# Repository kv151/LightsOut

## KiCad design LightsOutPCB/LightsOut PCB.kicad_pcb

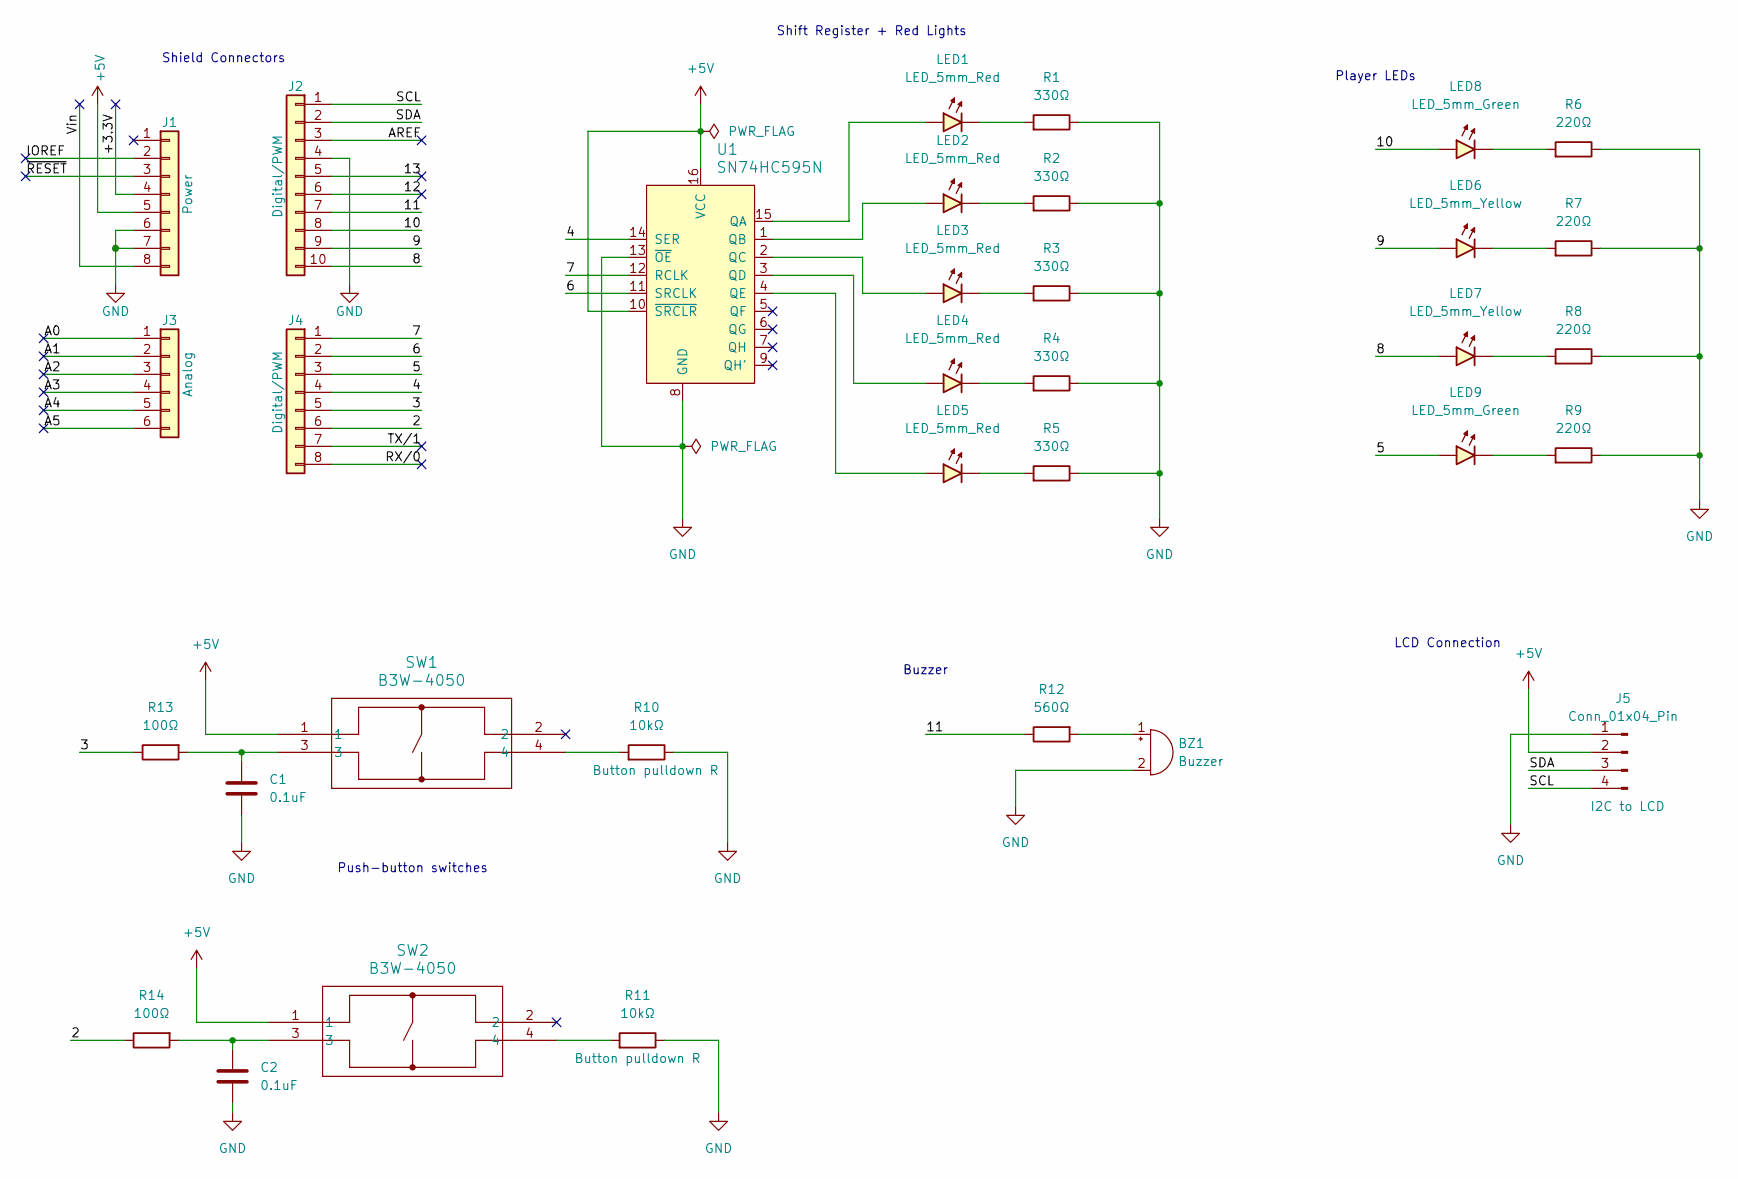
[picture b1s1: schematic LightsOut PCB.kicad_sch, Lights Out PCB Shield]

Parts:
BZ1: Buzzer; MagneticBuzzer_StarMicronics_TMB
C1, C2: 0.1uF; C_Radial_D5.0mm_H7.0mm_P2.00mm
J1: Power; PinSocket_1x08_P2.54mm_Vertical
J2: Digital/PWM; PinSocket_1x10_P2.54mm_Vertical
J3: Analog; PinSocket_1x06_P2.54mm_Vertical
J4: Digital/PWM; PinSocket_1x08_P2.54mm_Vertical
J5: Conn_01x04_Pin; PinSocket_1x04_P2.00mm_Vertical
LED1, LED2, LED3, LED4, LED5: LED_5mm_Red; LED_D5.0mm
LED6, LED7: LED_5mm_Yellow; LED_D5.0mm
LED8, LED9: LED_5mm_Green; LED_D5.0mm
R1, R2, R3, R4, R5: 330Ω; R_Axial_DIN0204_L3.6mm_D1.6mm_P7.62mm_Horizontal
R6, R7, R8, R9: 220Ω; R_Axial_DIN0204_L3.6mm_D1.6mm_P7.62mm_Horizontal
R10, R11: 10kΩ; R_Axial_DIN0204_L3.6mm_D1.6mm_P7.62mm_Horizontal
R12: 560Ω; R_Axial_DIN0204_L3.6mm_D1.6mm_P7.62mm_Horizontal
R13, R14: 100Ω; R_Axial_DIN0204_L3.6mm_D1.6mm_P7.62mm_Horizontal
SW1, SW2: B3W-4050; SW_B3W-4050_OMR
U1: SN74HC595N; DIP-16_W7.62mm; MPN SN74HC595N; Digi-Key_PN 296-1600-5-ND

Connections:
+5V: J1.5, J5.2, SW1.1, SW2.1, U1.10 (~SRCLR), U1.16 (VCC)
/2: J4.6, R14.2
/3: J4.5, R13.2
/4: J4.4, U1.14 (SER)
/5: J4.3, LED9.2 (A)
/6: J4.2, U1.11 (SRCLK)
/7: J4.1, U1.12 (RCLK)
/8: J2.10, LED7.2 (A)
/9: J2.9, LED6.2 (A)
/10: J2.8, LED8.2 (A)
/11: J2.7, R12.2
/12: J2.6
/13: J2.5
/+3.3V: J1.4
/A0: J3.1
/A1: J3.2
/A2: J3.3
/A3: J3.4
/A4: J3.5
/A5: J3.6
/AREF: J2.3
/IOREF: J1.2
/RX/0: J4.8
/SCL: J2.1, J5.4
/SDA: J2.2, J5.3
/TX/1: J4.7
/Vin: J1.8
/~RESET: J1.3
GND: BZ1.2 (-), C1.2, C2.2, J1.6, J1.7, J2.4, J5.1, R1.2, R2.2, R3.2, R4.2, R5.2, R6.2, R7.2, R8.2, R9.2, R10.2, R11.2, U1.8 (GND), U1.13 (~OE)
unnamed: BZ1.1 (+), R12.1
unnamed: C1.1, R13.1, SW1.3
unnamed: C2.1, R14.1, SW2.3
unnamed: LED1.2 (A), U1.15 (QA)
unnamed: LED1.1 (K), R1.1
unnamed: LED2.2 (A), U1.1 (QB)
unnamed: LED2.1 (K), R2.1
unnamed: LED3.2 (A), U1.2 (QC)
unnamed: LED3.1 (K), R3.1
unnamed: LED4.2 (A), U1.3 (QD)
unnamed: LED4.1 (K), R4.1
unnamed: LED5.2 (A), U1.4 (QE)
unnamed: LED5.1 (K), R5.1
unnamed: LED6.1 (K), R7.1
unnamed: LED7.1 (K), R8.1
unnamed: LED8.1 (K), R6.1
unnamed: LED9.1 (K), R9.1
unnamed: R10.1, SW1.4
unnamed: R11.1, SW2.4

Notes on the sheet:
Shield Connectors
Buzzer
Shift Register + Red Lights
LCD Connection
Push-button switches
Player LEDs

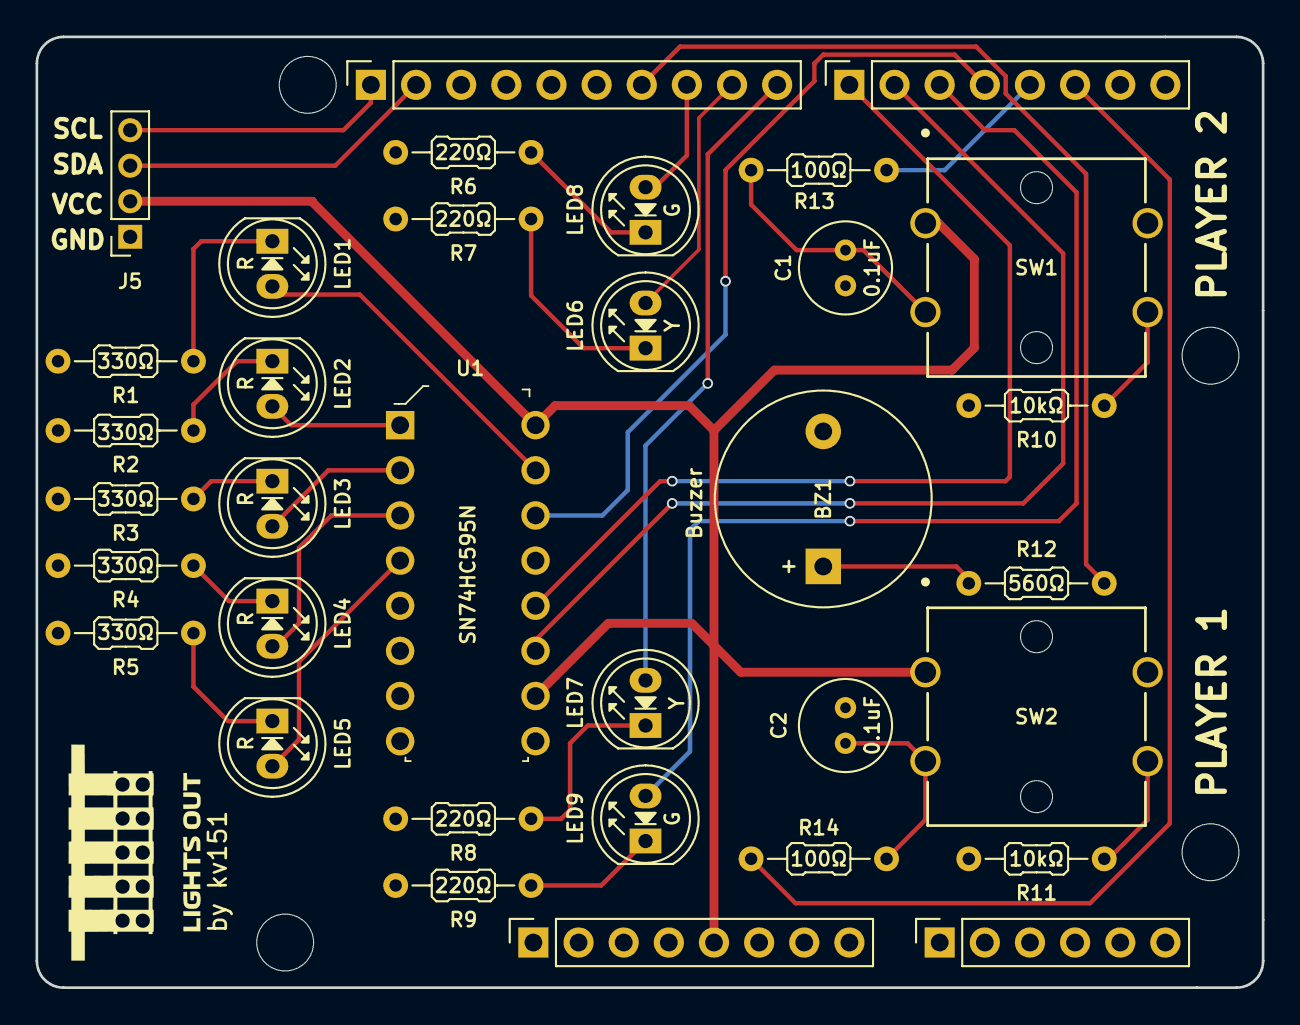
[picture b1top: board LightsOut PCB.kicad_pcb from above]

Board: 2 copper layers, 69.0 x 53.5 mm, 38 parts (0 on the bottom side), 33 nets.

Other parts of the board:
MH1, MH2, MH3, MH4: MountingHole_3.2mm

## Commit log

2026-04-04 updated reaction time measure
2026-04-04 try interrupt timers for button detection
2026-04-04 implemnted interrupt timers to debug
2026-04-04 implemented isr but need to change delay logic
2026-04-04 implemented state machine for game logic
2026-04-04 fixed incorrect state for ISRs
2026-04-04 fixed bug with clearing game state before new game
2026-04-04 fixed jump start alert
2026-04-04 implemented I2C LCD display code
2026-04-04 implemented buzzer and LCD
2026-04-05 debugging lcd and buttons
2026-04-05 inverted high/low logic for buttons to try to debug
2026-04-05 fixed lcd printing logic
2026-04-05 fixed shift register pins not set
2026-04-05 cleaned up debug messages
2026-04-05 updated lcd messages
2026-04-05 added pcb files and libraries
2026-04-05 add pcb files
2026-04-05 completed schematic
2026-04-05 finished initial placement
2026-04-05 set main traces
2026-04-05 routing complete
2026-04-05 Poured GND poly
2026-04-05 info on front silkscreen
2026-04-05 added info to silkscreen
2026-04-06 Finsihed PCB design
2026-04-06 finished pcb design
2026-04-06 tweaked lcd message
